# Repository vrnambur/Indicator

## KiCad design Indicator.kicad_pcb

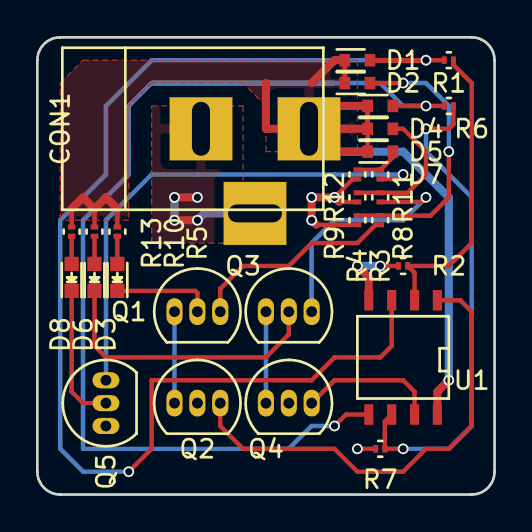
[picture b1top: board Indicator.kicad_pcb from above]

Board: 2 copper layers, 25.4 x 25.4 mm, 28 parts (0 on the bottom side), 22 nets.

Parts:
CON1: BARREL_JACK
D1: 5V; SOD-523
D2: 1V; SOD-523
D3, D6, D8: LED; LED-0603
D4: 7V; SOD-523
D5: 3.3V; SOD-523
D7: 6V; SOD-523
Q1, Q3, Q5: 2SC1815; TO-92_Inline_Narrow_Oval
Q2, Q4: 2SA1016; TO-92_Inline_Narrow_Oval
R1, R6: 2; R_0201
R2, R4, R7, R9, R12: 1k; R_0201
R3, R8, R11: 100k; R_0201
R5: 90; R_0201
R10: 200; R_0201
R13: 450; R_0201
U1: LM2903; SOIC-8-N

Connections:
GND: CON1.2, CON1.3, Q2.2, Q4.2, Q5.1, R2.2, R3.2, R7.2, R8.2, R11.2, U1.4
unnamed: CON1.1, D1.1, D2.1, D4.1, D5.1, D7.1, R5.1, R10.1, R13.1, U1.8
unnamed: D1.2, R1.1, U1.3
unnamed: D2.2, R3.1, R4.2
unnamed: D3.1, Q1.2
unnamed: D3.2, R5.2
unnamed: D4.2, R6.1, U1.5
unnamed: D5.2, R8.1, R9.2
unnamed: D6.1, Q3.2
unnamed: D6.2, R10.2
unnamed: D7.2, R11.1, R12.2
unnamed: D8.1, Q5.2
unnamed: D8.2, R13.2
unnamed: Q1.1, Q2.1
unnamed: Q1.3, R4.1
unnamed: Q2.3, U1.1
unnamed: Q3.1, Q4.1
unnamed: Q3.3, R9.1
unnamed: Q4.3, U1.7
unnamed: Q5.3, R12.1
unnamed: R1.2, R2.1, U1.2
unnamed: R6.2, R7.1, U1.6

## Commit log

2015-08-25 Initial Commit: Main portion of the schematic is complete.
    An trial layout has also been performed.
    Real components need to be sourced and made footprints for.
